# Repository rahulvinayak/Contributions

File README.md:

# Contributions

---

A collaborative repository for **Electronics-related work**, including:  
- 📐 **KiCad Schematics** – Circuit designs, PCB layouts, libraries  
- ⚡ **Embedded Code** – Firmware for microcontrollers, drivers, and RTOS examples  
- 🔧 **Hardware Notes** – Datasheets, application notes, and design references  

---

## 📂 Repository Structure  

```

  contributions/
  │
  ├── 📂 Embedded Codes/               # Firmware and embedded C/C++/Arduino/STM32/ESP32 code
  ├── 📂 kicad/                        # KiCad projects, schematics, PCB layouts
  ├── 📂 Libraries and Dependencies/     # Libraries and Dependencies used for the Codes and Projects
  ├── 📂 docs/                         # Datasheets, references, and documentation
  └── 📂 README.md                     # You are here

````

---

## 🚀 Getting Started  

1. **Clone this repo**  
```bash
   git clone https://github.com/your-username/contributions.git
   cd contributions
```

2. **Explore folders**

   * Open `.kicad_pcb` or `.sch` files with [KiCad](https://kicad.org/).
   * Build embedded code with **Arduino IDE**, **STM32CubeIDE**, **ESP IDF**, or **PlatformIO**.

---

## 🛠 Tools & Dependencies

* [KiCad](https://kicad.org/) (schematics & PCB design)
* [Arduino IDE](https://www.arduino.cc/en/software) / [PlatformIO](https://platformio.org/)
* [STM32CubeIDE](https://www.st.com/en/development-tools/stm32cubeide.html)
* [ESP-IDF](https://docs.espressif.com/projects/esp-idf/) for ESP32 projects

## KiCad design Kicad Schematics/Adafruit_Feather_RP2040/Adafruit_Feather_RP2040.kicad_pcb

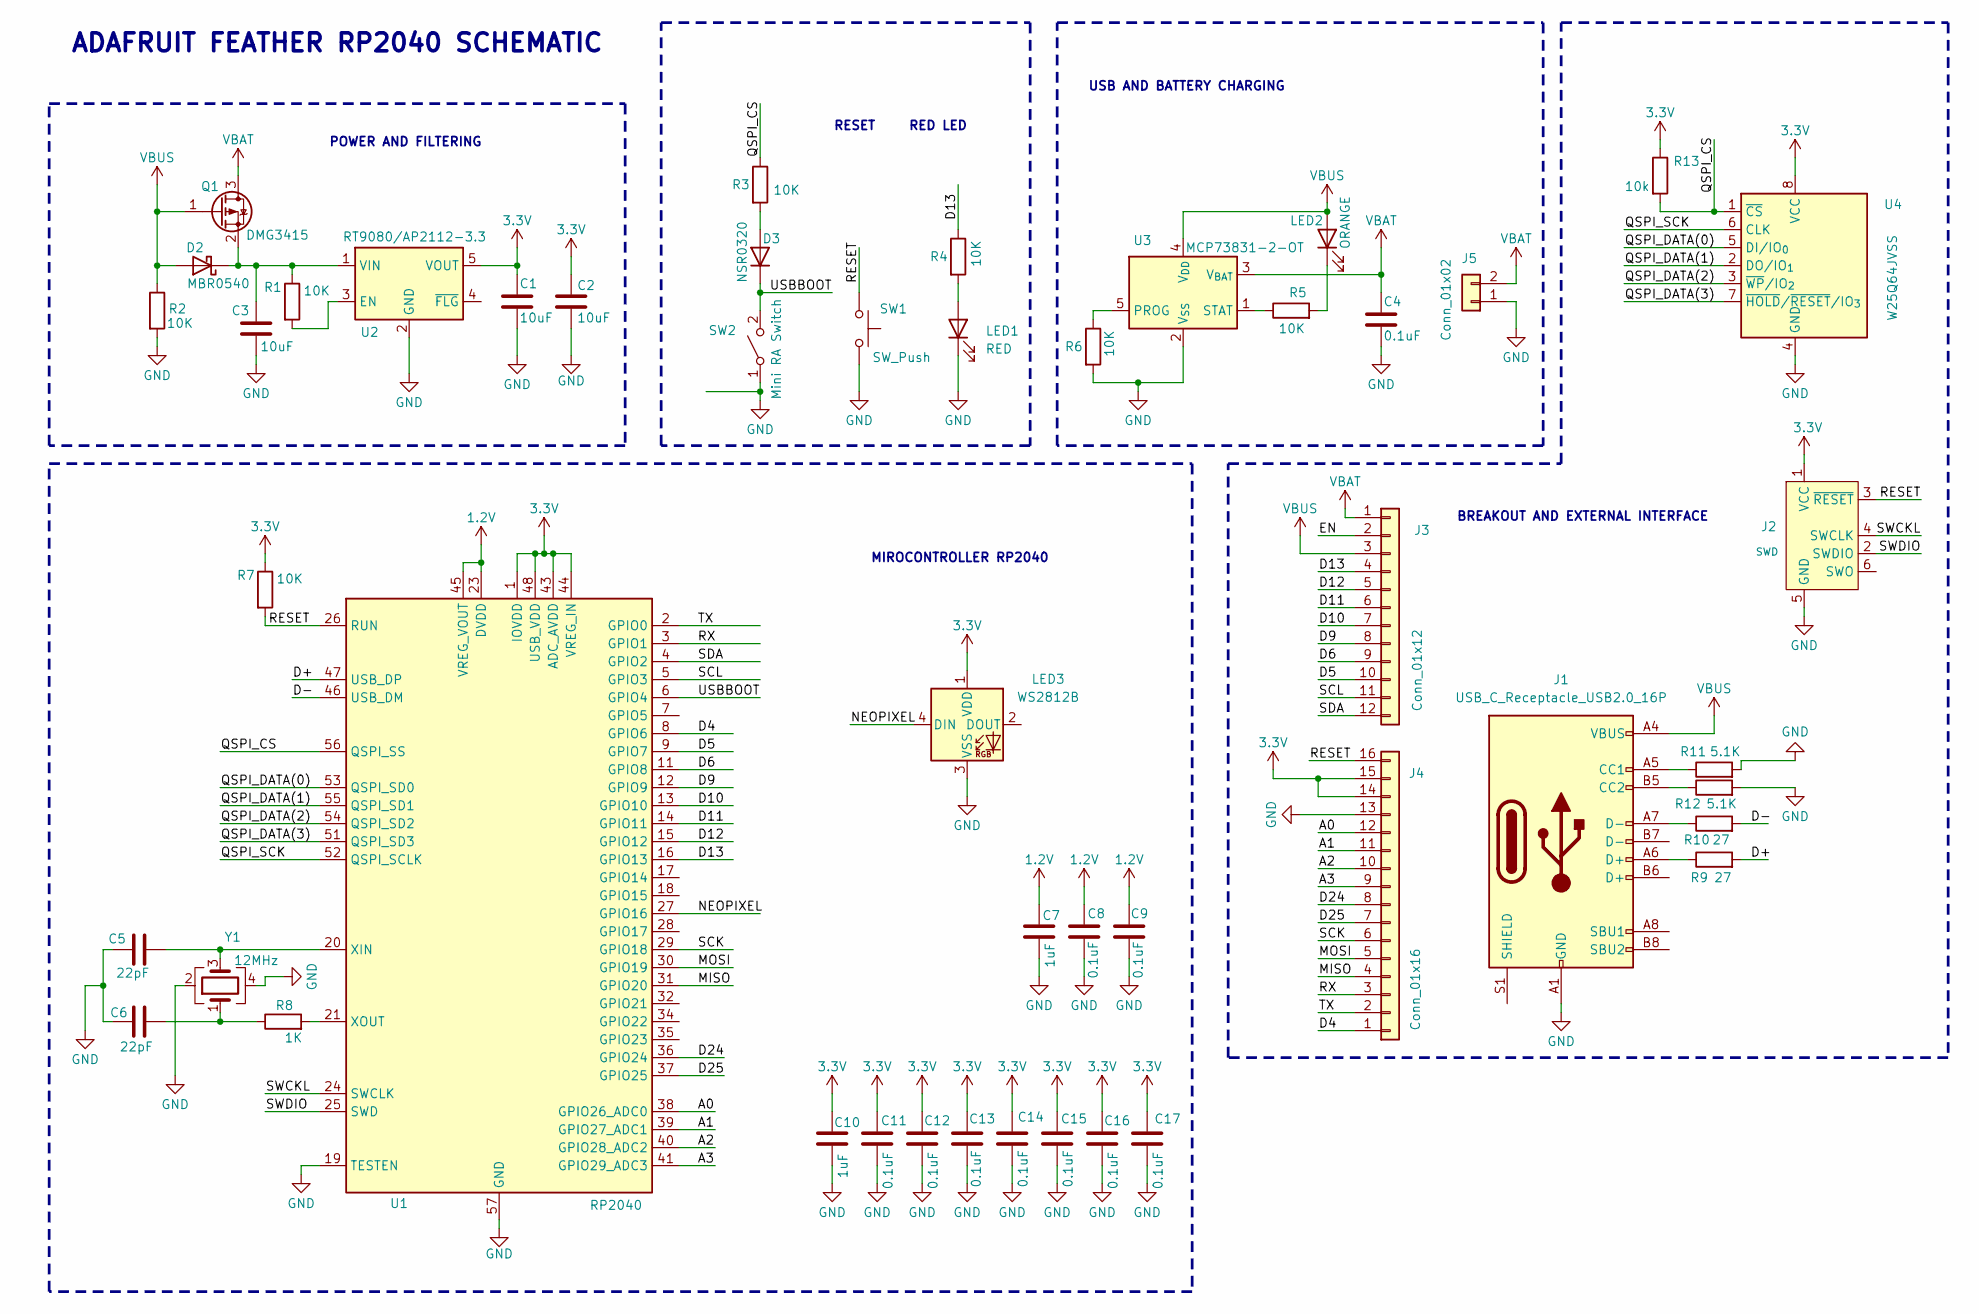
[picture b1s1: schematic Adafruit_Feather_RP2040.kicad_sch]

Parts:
C1, C2, C3: 10uF; C_0603_1608Metric
C4, C8, C9, C11, C12, C13, C14, C15, C16, C17: 0.1uF; C_0603_1608Metric
C5, C6: 22pF; C_0603_1608Metric
C7, C10: 1uF; C_0603_1608Metric
D2: MBR0540; D_SOD-123
D3: NSR0320; D_SOD-123
J1: USB_C_Receptacle_USB2.0_16P; USB_C_Receptacle_GCT_USB4105-xx-A_16P_TopMnt_Horizontal
J2: SWD; Tag-Connect_TC2030-IDC-NL_2x03_P1.27mm_Vertical
J3: Conn_01x12; PinHeader_1x12_P2.54mm_Vertical
J4: Conn_01x16; PinHeader_1x16_P2.54mm_Vertical
J5: Conn_01x02; JST_EH_S2B-EH_1x02_P2.50mm_Horizontal
LED1: RED; LED_0603_1608Metric
LED2: ORANGE; LED_0603_1608Metric
LED3: WS2812B; LED_WS2812B_PLCC4_5.0x5.0mm_P3.2mm
Q1: DMG3415; SOT-23-3
R1, R2, R3, R4, R5, R6, R7: 10K; R_0603_1608Metric
R8: 1K; R_0603_1608Metric
R9, R10: 27; R_0603_1608Metric
R11, R12: 5.1K; R_0603_1608Metric
R13: 10k; R_0603_1608Metric
SW1: SW_Push; SW_SPST_PTS810
SW2: Mini RA Switch; SW_SPST_PTS810
U1: RP2040; QFN-56-1EP_7x7mm_P0.4mm_EP3.2x3.2mm
U2: RT9080/AP2112-3.3; TSOT-23-5
U3: MCP73831-2-OT; SOT-23-5
U4: W25Q64JVSS; SOIC-8_5.3x5.3mm_P1.27mm
Y1: 12MHz; Crystal_SMD_3225-4Pin_3.2x2.5mm

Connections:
1.2V: C7.2, C8.2, C9.2, U1.23 (DVDD), U1.45 (VREG_VOUT), U1.50 (DVDD)
3.3V: C1.1, C2.1, C10.2, C11.2, C12.2, C13.2, C14.2, C15.2, C16.2, C17.2, J2.1 (VCC), J4.14, J4.15, LED3.1 (VDD), R7.1, R13.1, U1.1 (IOVDD), U1.10 (IOVDD), U1.22 (IOVDD), U1.33 (IOVDD), U1.42 (IOVDD), U1.43 (ADC_AVDD), U1.44 (VREG_IN), U1.48 (USB_VDD), U1.49 (IOVDD), U2.5 (VOUT), U4.8 (VCC)
/A0: J4.12, U1.38 (GPIO26_ADC0)
/A1: J4.11, U1.39 (GPIO27_ADC1)
/A2: J4.10, U1.40 (GPIO28_ADC2)
/A3: J4.9, U1.41 (GPIO29_ADC3)
/D4: J4.1, U1.8 (GPIO6)
/D5: J3.10, U1.9 (GPIO7)
/D6: J3.9, U1.11 (GPIO8)
/D9: J3.8, U1.12 (GPIO9)
/D10: J3.7, U1.13 (GPIO10)
/D11: J3.6, U1.14 (GPIO11)
/D12: J3.5, U1.15 (GPIO12)
/D13: J3.4, R4.1, U1.16 (GPIO13)
/D24: J4.8, U1.36 (GPIO24)
/D25: J4.7, U1.37 (GPIO25)
/D+: R9.2, U1.47 (USB_DP)
/D-: R10.2, U1.46 (USB_DM)
/EN: J3.2
/MISO: J4.4, U1.31 (GPIO20)
/MOSI: J4.5, U1.30 (GPIO19)
/NEOPIXEL: LED3.4 (DIN), U1.27 (GPIO16)
/QSPI_CS: R3.1, R13.2, U1.56 (QSPI_SS), U4.1 (~CS)
/QSPI_DATA(0): U1.53 (QSPI_SD0), U4.5 (DI/IO_{0})
/QSPI_DATA(1): U1.55 (QSPI_SD1), U4.2 (DO/IO_{1})
/QSPI_DATA(2): U1.54 (QSPI_SD2), U4.3 (~WP/IO_{2})
/QSPI_DATA(3): U1.51 (QSPI_SD3), U4.7 (~HOLD/~RESET/IO_{3})
/QSPI_SCK: U1.52 (QSPI_SCLK), U4.6 (CLK)
/RESET: J2.3 (~RESET), J4.16, R7.2, SW1.1, U1.26 (RUN)
/RX: J4.3, U1.3 (GPIO1)
/SCK: J4.6, U1.29 (GPIO18)
/SCL: J3.11, U1.5 (GPIO3)
/SDA: J3.12, U1.4 (GPIO2)
/SWCKL: J2.4 (SWCLK), U1.24 (SWCLK)
/SWDIO: J2.2 (SWDIO), U1.25 (SWD)
/TX: J4.2, U1.2 (GPIO0)
/USBBOOT: D3.1 (K), SW2.2 (B), U1.6 (GPIO4)
GND: C1.2, C2.2, C3.2, C4.2, C5.1, C6.1, C7.1, C8.1, C9.1, C10.1, C11.1, C12.1, C13.1, C14.1, C15.1, C16.1, C17.1, J1.A1 (GND), J1.A12 (GND), J1.B1 (GND), J1.B12 (GND), J2.5 (GND), J4.13, J5.1, LED1.1 (K), LED3.3 (VSS), R2.2, R6.2, R11.2, R12.2, SW1.2, SW2.1 (A), U1.19 (TESTEN), U1.57 (GND), U2.2 (GND), U3.2 (V_{SS}), U4.4 (GND), Y1.2, Y1.4
unnamed: C6.2, R8.1, Y1.1
unnamed: C3.1, D2.1 (K), Q1.2 (S), R1.1, U2.1 (VIN)
unnamed: D3.2 (A), R3.2
unnamed: J1.A5 (CC1), R11.1
unnamed: J1.B5 (CC2), R12.1
unnamed: J1.A6 (D+), R9.1
unnamed: J1.A7 (D-), R10.1
unnamed: LED1.2 (A), R4.2
unnamed: LED2.1 (K), R5.2
unnamed: C5.2, U1.20 (XIN), Y1.3
unnamed: R8.2, U1.21 (XOUT)
unnamed: R1.2, U2.3 (EN)
unnamed: R6.1, U3.5 (PROG)
unnamed: R5.1, U3.1 (STAT)
VBAT: C4.1, J3.1, J5.2, Q1.3 (D), U3.3 (V_{BAT})
VBUS: D2.2 (A), J1.A4 (VBUS), J1.A9 (VBUS), J1.B4 (VBUS), J1.B9 (VBUS), J3.3, LED2.2 (A), Q1.1 (G), R2.1, U3.4 (V_{DD})

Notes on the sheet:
USB AND BATTERY CHARGING
MIROCONTROLLER RP2040
POWER AND FILTERING
BREAKOUT AND EXTERNAL INTERFACE
RESET RED LED
ADAFRUIT FEATHER RP2040 SCHEMATIC

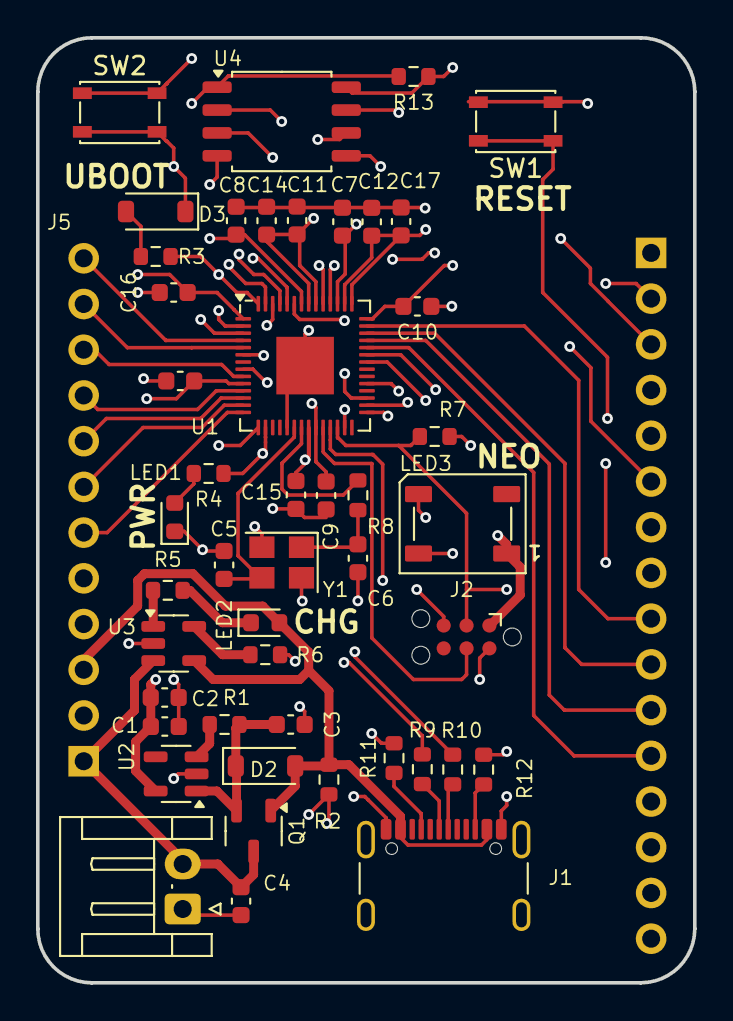
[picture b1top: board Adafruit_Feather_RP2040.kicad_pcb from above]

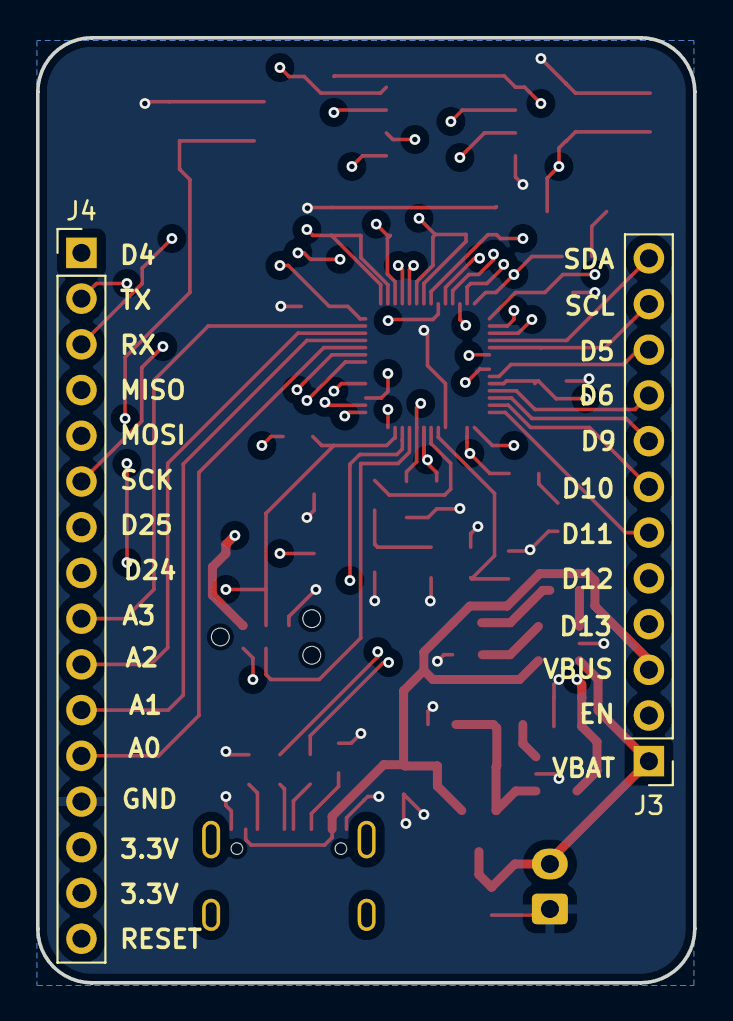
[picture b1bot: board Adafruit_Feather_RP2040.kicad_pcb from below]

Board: 4 copper layers, 36.5 x 52.5 mm, 48 parts (2 on the bottom side), 53 nets.

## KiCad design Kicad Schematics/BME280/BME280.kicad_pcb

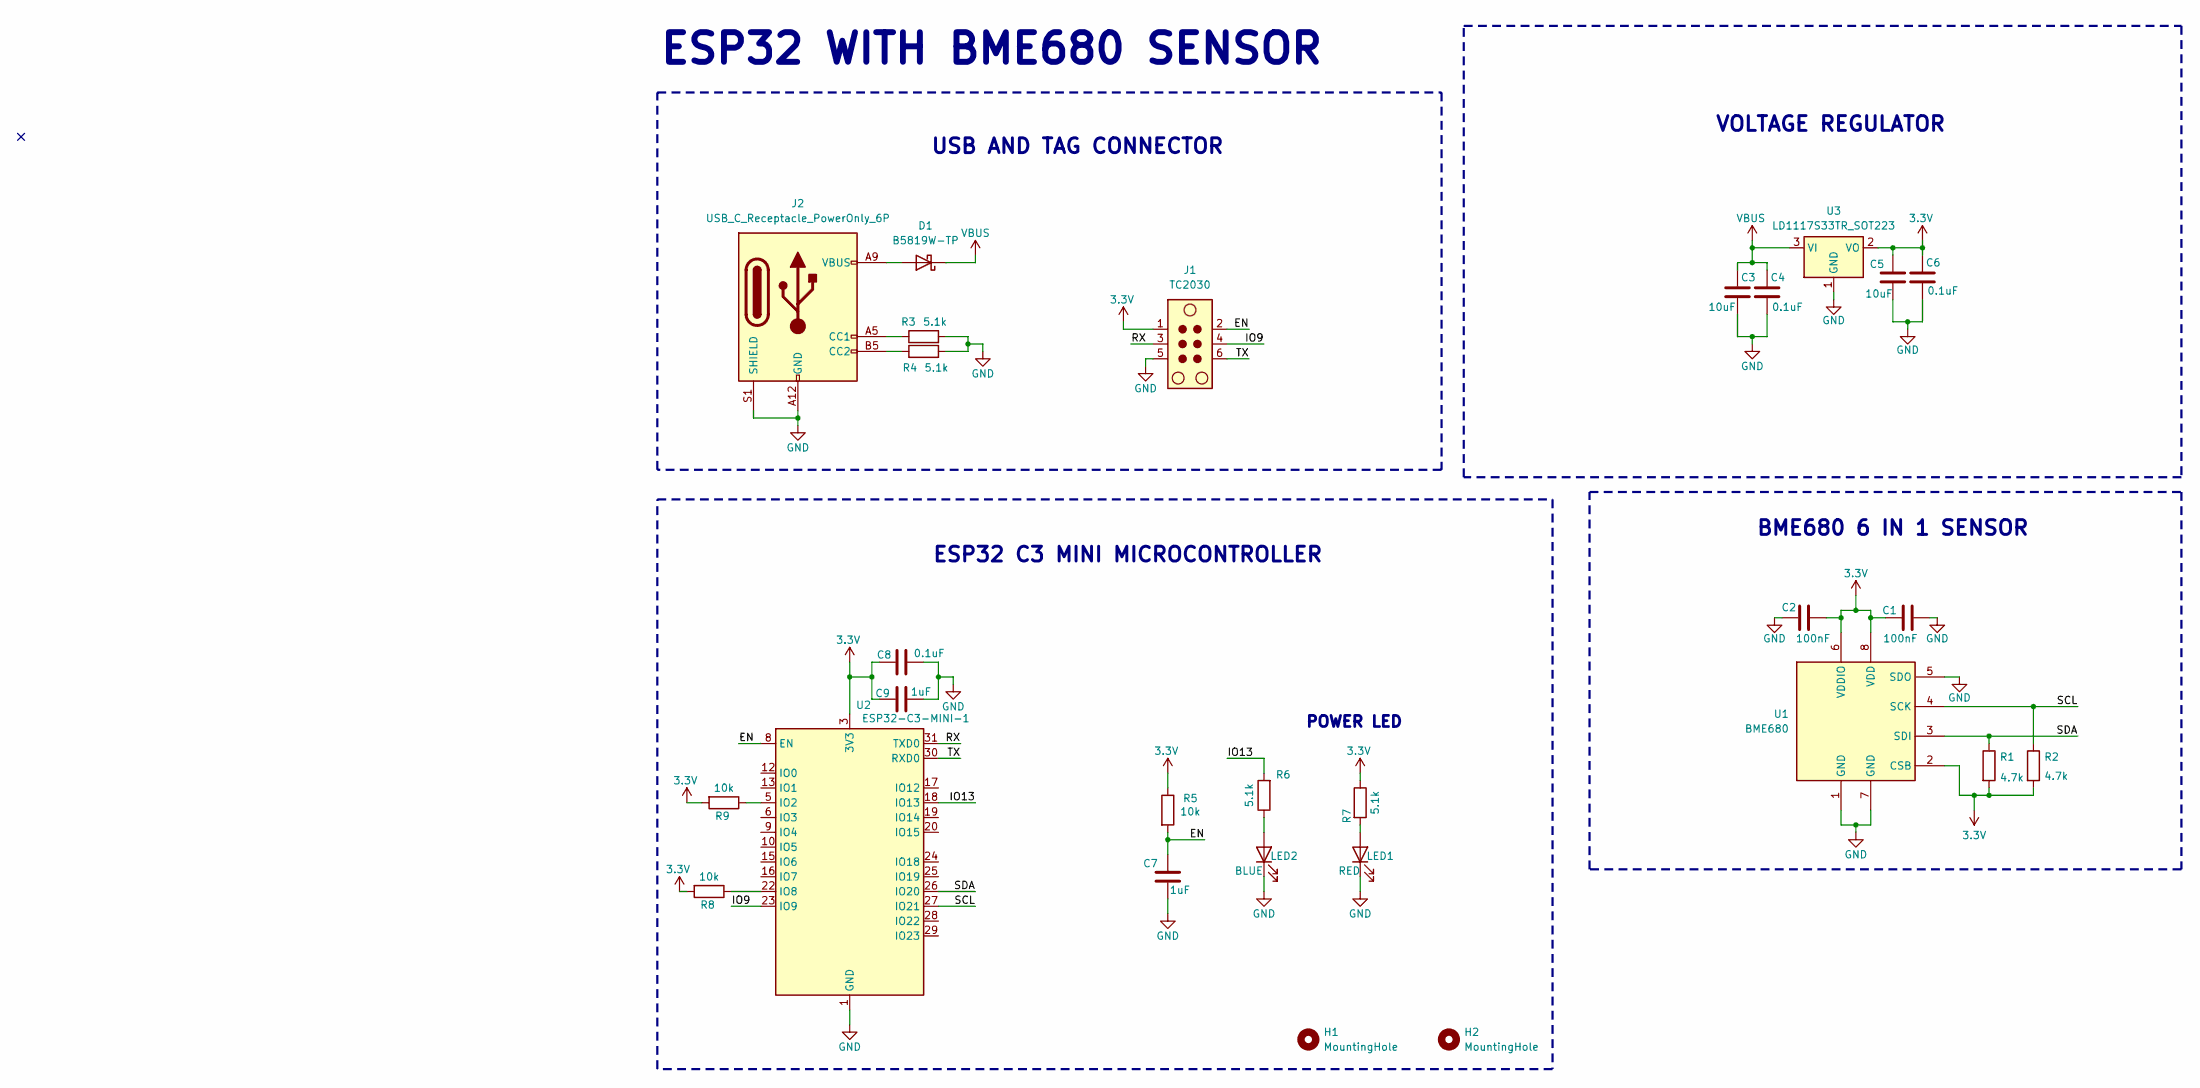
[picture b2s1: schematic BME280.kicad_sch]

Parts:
C1, C2: 100nF; C_0603_1608Metric
C3, C5: 10uF; C_0603_1608Metric
C4, C6, C8: 0.1uF; C_0603_1608Metric
C7, C9: 1uF; C_0603_1608Metric
D1: B5819W-TP; D_SOD-123
H1, H2: MountingHole; MountingHole_2.5mm
J1: TC2030; Tag-Connect_TC2030-IDC-NL_2x03_P1.27mm_Vertical
J2: USB_C_Receptacle_PowerOnly_6P; USB_C_Receptacle_GCT_USB4125-xx-x_6P_TopMnt_Horizontal
LED1: RED; LED_0603_1608Metric
LED2: BLUE; LED_0603_1608Metric
R1, R2: 4.7k; R_0603_1608Metric
R3, R4, R6, R7: 5.1k; R_0603_1608Metric
R5, R8, R9: 10k; R_0603_1608Metric
U1: BME680; Bosch_LGA-8_3x3mm_P0.8mm_ClockwisePinNumbering
U2: ESP32-C3-MINI-1; ESP32-C6-MINI-1
U3: LD1117S33TR_SOT223; SOT-223-3_TabPin2

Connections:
3.3V: C1.1, C2.2, C5.2, C6.2, C8.2, C9.2, J1.1, R1.2, R2.2, R5.1, R7.1, R8.2, R9.2, U1.2 (CSB), U1.6 (VDDIO), U1.8 (VDD), U2.3 (3V3), U3.2 (VO)
/EN: C7.1, J1.2, R5.2, U2.8 (EN)
/IO9: J1.4, U2.23 (IO9)
/IO13: R6.2, U2.18 (IO13)
/RX: J1.3, U2.31 (TXD0)
/SCL: R2.1, U1.4 (SCK), U2.27 (IO21)
/SDA: R1.1, U1.3 (SDI), U2.26 (IO20)
/TX: J1.6, U2.30 (RXD0)
GND: C1.2, C2.1, C3.1, C4.1, C5.1, C6.1, C7.2, C8.1, C9.1, J1.5, J2.A12 (GND), J2.B12 (GND), J2.S1 (SHIELD), LED1.1 (K), LED2.1 (K), R3.2, R4.2, U1.1 (GND), U1.5 (SDO), U1.7 (GND), U2.1 (GND), U2.2 (GND), U2.11 (GND), U2.14 (GND), U2.36 (GND), U2.37 (GND), U2.38 (GND), U2.39 (GND), U2.40 (GND), U2.41 (GND), U2.42 (GND), U2.43 (GND), U2.44 (GND), U2.45 (GND), U2.46 (GND), U2.47 (GND), U2.48 (GND), U2.49 (GND), U2.50 (GND), U2.51 (GND), U2.52 (GND), U2.53 (GND), U3.1 (GND)
unnamed: D1.2 (A), J2.A9 (VBUS), J2.B9 (VBUS)
unnamed: J2.A5 (CC1), R3.1
unnamed: J2.B5 (CC2), R4.1
unnamed: LED1.2 (A), R7.2
unnamed: LED2.2 (A), R6.1
unnamed: R9.1, U2.5 (IO2)
unnamed: R8.1, U2.22 (IO8)
VBUS: C3.2, C4.2, D1.1 (K), U3.3 (VI)

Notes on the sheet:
VOLTAGE REGULATOR
USB AND TAG CONNECTOR
BME680 6 IN 1 SENSOR
ESP32 C3 MINI MICROCONTROLLER
ESP32 WITH BME680 SENSOR
POWER LED

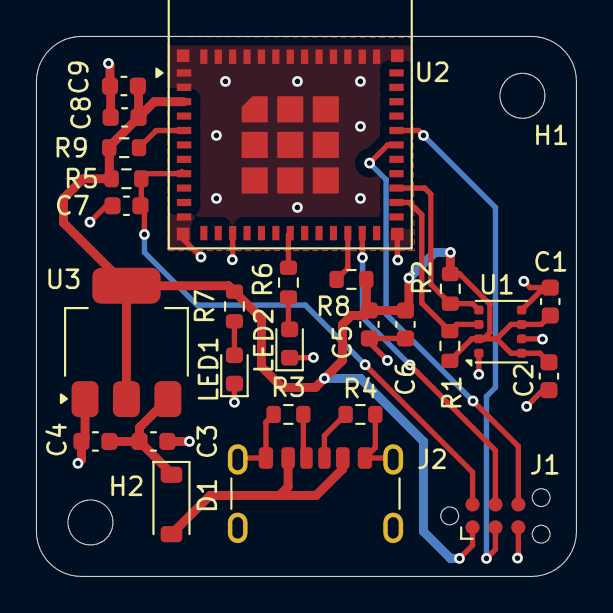
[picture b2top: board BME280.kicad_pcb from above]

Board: 2 copper layers, 30.0 x 30.0 mm, 28 parts (0 on the bottom side), 17 nets.

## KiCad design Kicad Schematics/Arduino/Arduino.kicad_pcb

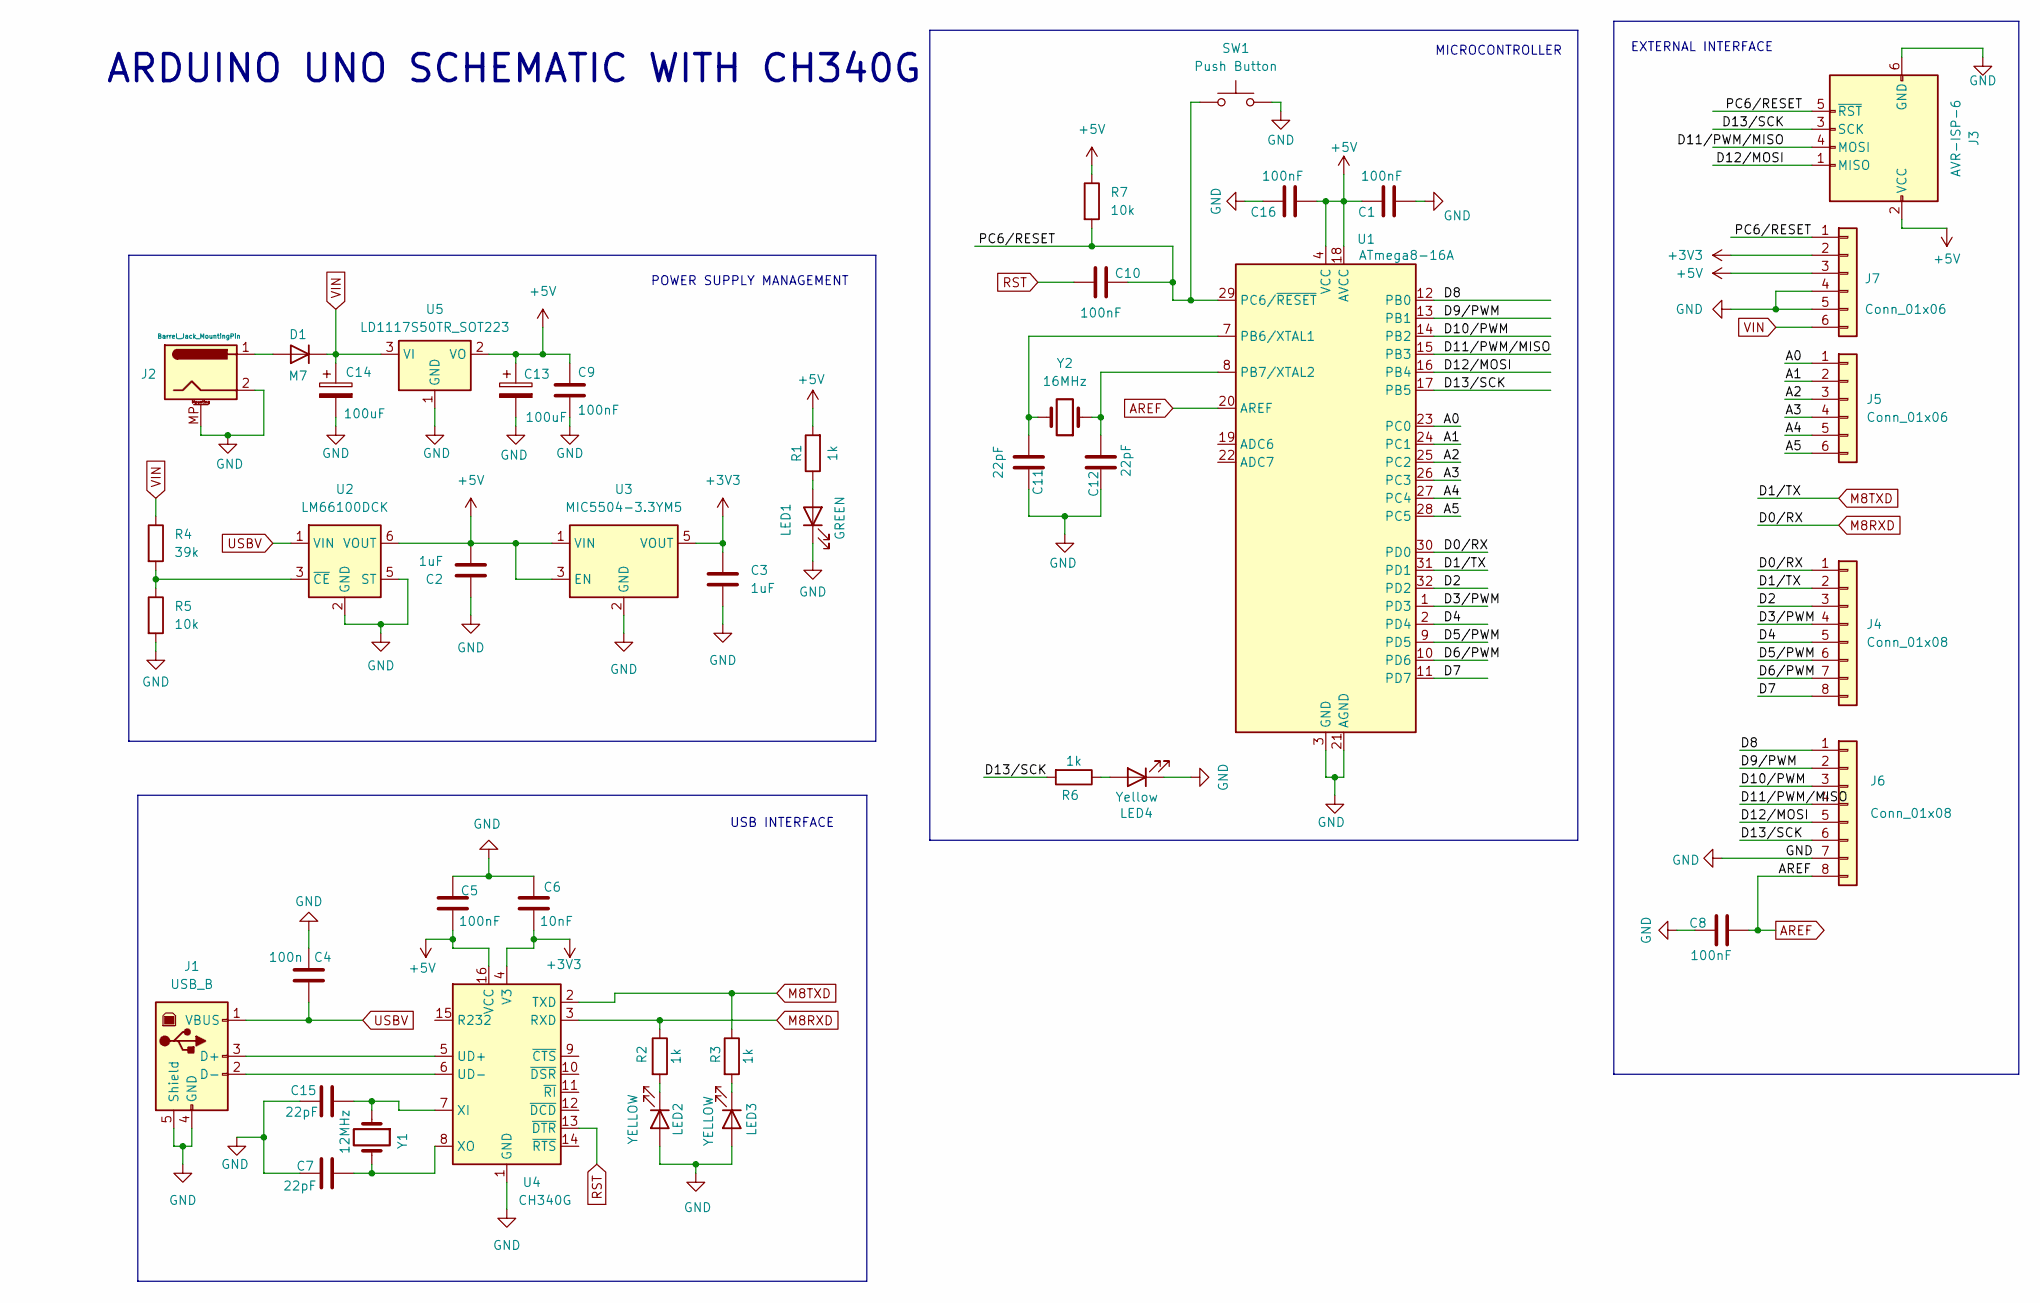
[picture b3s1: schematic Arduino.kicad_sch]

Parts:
C1, C5, C8, C9, C10, C16: 100nF; C_0603_1608Metric
C2, C3: 1uF; C_0603_1608Metric
C4: 100n; C_0603_1608Metric
C6: 10nF; C_0603_1608Metric
C7, C11, C12, C15: 22pF; C_0603_1608Metric
C13, C14: 100uF; C_Elec_6.3x5.8
D1: M7; D_SMA
J1: USB_B; USB_B_Lumberg_2411_02_Horizontal
J2: Barrel_Jack_MountingPin; BarrelJack_Horizontal
J3: AVR-ISP-6; PinHeader_2x03_P2.54mm_Vertical
J4, J6: Conn_01x08; PinSocket_1x08_P2.54mm_Vertical
J5, J7: Conn_01x06; PinSocket_1x06_P2.54mm_Vertical
LED1: GREEN; LED_0603_1608Metric
LED2, LED3: YELLOW; LED_0603_1608Metric
LED4: Yellow; LED_0603_1608Metric
R1, R2, R3, R6: 1k; R_0603_1608Metric
R4: 39k; R_0603_1608Metric
R5, R7: 10k; R_0603_1608Metric
SW1: Push Button; SW_SPST_PTS645
U1: ATmega8-16A; TQFP-32_7x7mm_P0.8mm
U2: LM66100DCK; SOT-363_SC-70-6
U3: MIC5504-3.3YM5; SOT-23-5
U4: CH340G; SO-16_5.3x10.2mm_P1.27mm
U5: LD1117S50TR_SOT223; SOT-223-3_TabPin2
Y1: 12MHz; Crystal_SMD_HC49-SD
Y2: 16MHz; Crystal_SMD_HC49-SD

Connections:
+3V3: C3.1, C6.2, J7.2, U3.5 (VOUT), U4.4 (V3)
+5V: C1.2, C2.2, C5.2, C9.1, C13.1, C16.1, J3.2 (VCC), J7.3, R1.2, R7.1, U1.4 (VCC), U1.6 (VCC), U1.18 (AVCC), U2.6 (VOUT), U3.1 (VIN), U3.3 (EN), U4.16 (VCC), U5.2 (VO)
/A0: J5.1, U1.23 (PC0)
/A1: J5.2, U1.24 (PC1)
/A2: J5.3, U1.25 (PC2)
/A3: J5.4, U1.26 (PC3)
/A4: J5.5, U1.27 (PC4)
/A5: J5.6, U1.28 (PC5)
/D2: J4.3, U1.32 (PD2)
/D3/PWM: J4.4, U1.1 (PD3)
/D4: J4.5, U1.2 (PD4)
/D5/PWM: J4.6, U1.9 (PD5)
/D6/PWM: J4.7, U1.10 (PD6)
/D7: J4.8, U1.11 (PD7)
/D8: J6.1, U1.12 (PB0)
/D9/PWM: J6.2, U1.13 (PB1)
/D10/PWM: J6.3, U1.14 (PB2)
/D11/PWM/MISO: J3.4 (MOSI), J6.4, U1.15 (PB3)
/D12/MOSI: J3.1 (MISO), J6.5, U1.16 (PB4)
/D13/SCK: J3.3 (SCK), J6.6, R6.2, U1.17 (PB5)
/PC6/RESET: C10.2, J3.5 (~RST), J7.1, R7.2, SW1.1, U1.29 (PC6/~RESET)
AREF: C8.2, J6.8, U1.20 (AREF)
GND: C1.1, C2.1, C3.2, C4.2, C5.1, C6.1, C7.2, C8.1, C9.2, C11.2, C12.2, C13.2, C14.2, C15.2, C16.2, J1.4 (GND), J1.5 (Shield), J2.2, J2.MP (MountPin), J3.6 (GND), J6.7, J7.4, J7.5, LED1.1 (K), LED2.2 (A), LED3.2 (A), LED4.1 (K), R5.2, SW1.2, U1.3 (GND), U1.5 (GND), U1.21 (AGND), U2.2 (GND), U2.5 (ST), U3.2 (GND), U4.1 (GND), U5.1 (GND)
M8RXD: J4.1, R2.1, U1.30 (PD0), U4.3 (RXD)
M8TXD: J4.2, R3.1, U1.31 (PD1), U4.2 (TXD)
unnamed: D1.2 (A), J2.1
unnamed: J1.3 (D+), U4.5 (UD+)
unnamed: J1.2 (D-), U4.6 (UD-)
unnamed: LED1.2 (A), R1.1
unnamed: LED2.1 (K), R2.2
unnamed: LED3.1 (K), R3.2
unnamed: LED4.2 (A), R6.1
unnamed: C11.1, U1.7 (PB6/XTAL1), Y2.2
unnamed: C12.1, U1.8 (PB7/XTAL2), Y2.1
unnamed: R4.2, R5.1, U2.3 (~CE)
unnamed: C15.1, U4.7 (XI), Y1.1
unnamed: C7.1, U4.8 (XO), Y1.2
RST: C10.1, U4.13 (~DTR)
USBV: C4.1, J1.1 (VBUS), U2.1 (VIN)
VIN: C14.1, D1.1 (K), J7.6, R4.1, U5.3 (VI)

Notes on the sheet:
EXTERNAL INTERFACE
ARDUINO UNO SCHEMATIC WITH CH340G
MICROCONTROLLER
POWER SUPPLY MANAGEMENT
USB INTERFACE

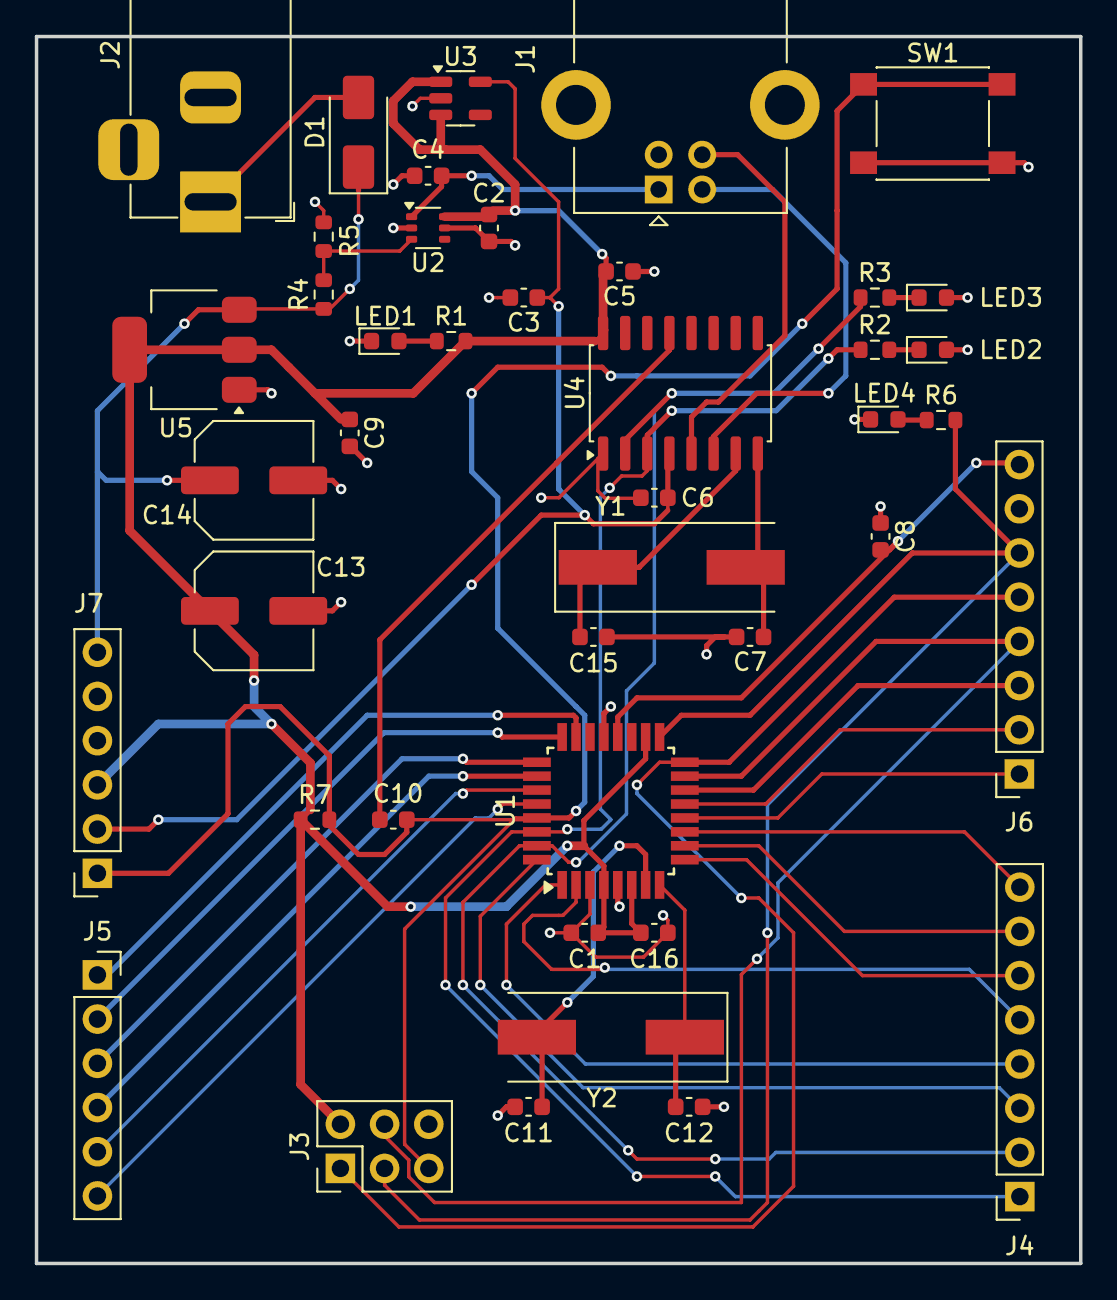
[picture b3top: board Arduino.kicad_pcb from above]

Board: 2 copper layers, 60.0 x 70.5 mm, 43 parts (0 on the bottom side), 40 nets.

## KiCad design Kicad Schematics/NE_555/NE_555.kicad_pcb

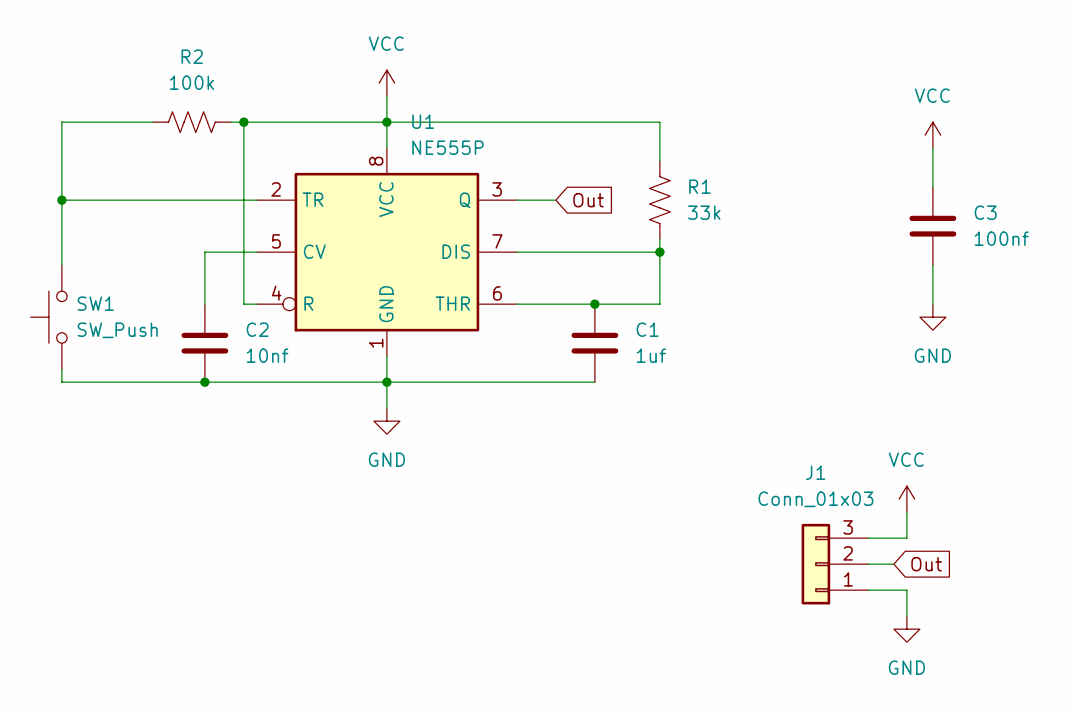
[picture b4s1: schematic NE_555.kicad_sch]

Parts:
C1: 1uf; C_0603_1608Metric
C2: 10nf; C_0603_1608Metric
C3: 100nf; C_0603_1608Metric
J1: Conn_01x03; PinHeader_1x03_P2.54mm_Vertical
R1: 33k; R_0603_1608Metric
R2: 100k; R_0603_1608Metric
SW1: SW_Push; SW_Push_1P1T_NO_Vertical_Wuerth_434133025816
U1: NE555P; SOIC-8_5.3x5.3mm_P1.27mm

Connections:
GND: C1.2, C2.2, C3.2, J1.1, SW1.1, U1.1 (GND)
unnamed: C2.1, U1.5 (CV)
unnamed: C1.1, R1.2, U1.6 (THR), U1.7 (DIS)
unnamed: R2.1, SW1.2, U1.2 (TR)
Out: J1.2, U1.3 (Q)
VCC: C3.1, J1.3, R1.1, R2.2, U1.4 (R), U1.8 (VCC)

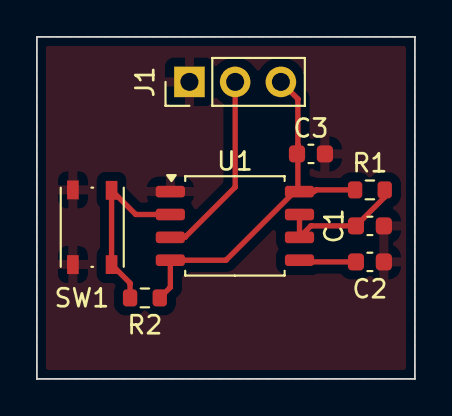
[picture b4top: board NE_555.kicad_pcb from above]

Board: 2 copper layers, 21.0 x 19.0 mm, 8 parts (0 on the bottom side), 6 nets.

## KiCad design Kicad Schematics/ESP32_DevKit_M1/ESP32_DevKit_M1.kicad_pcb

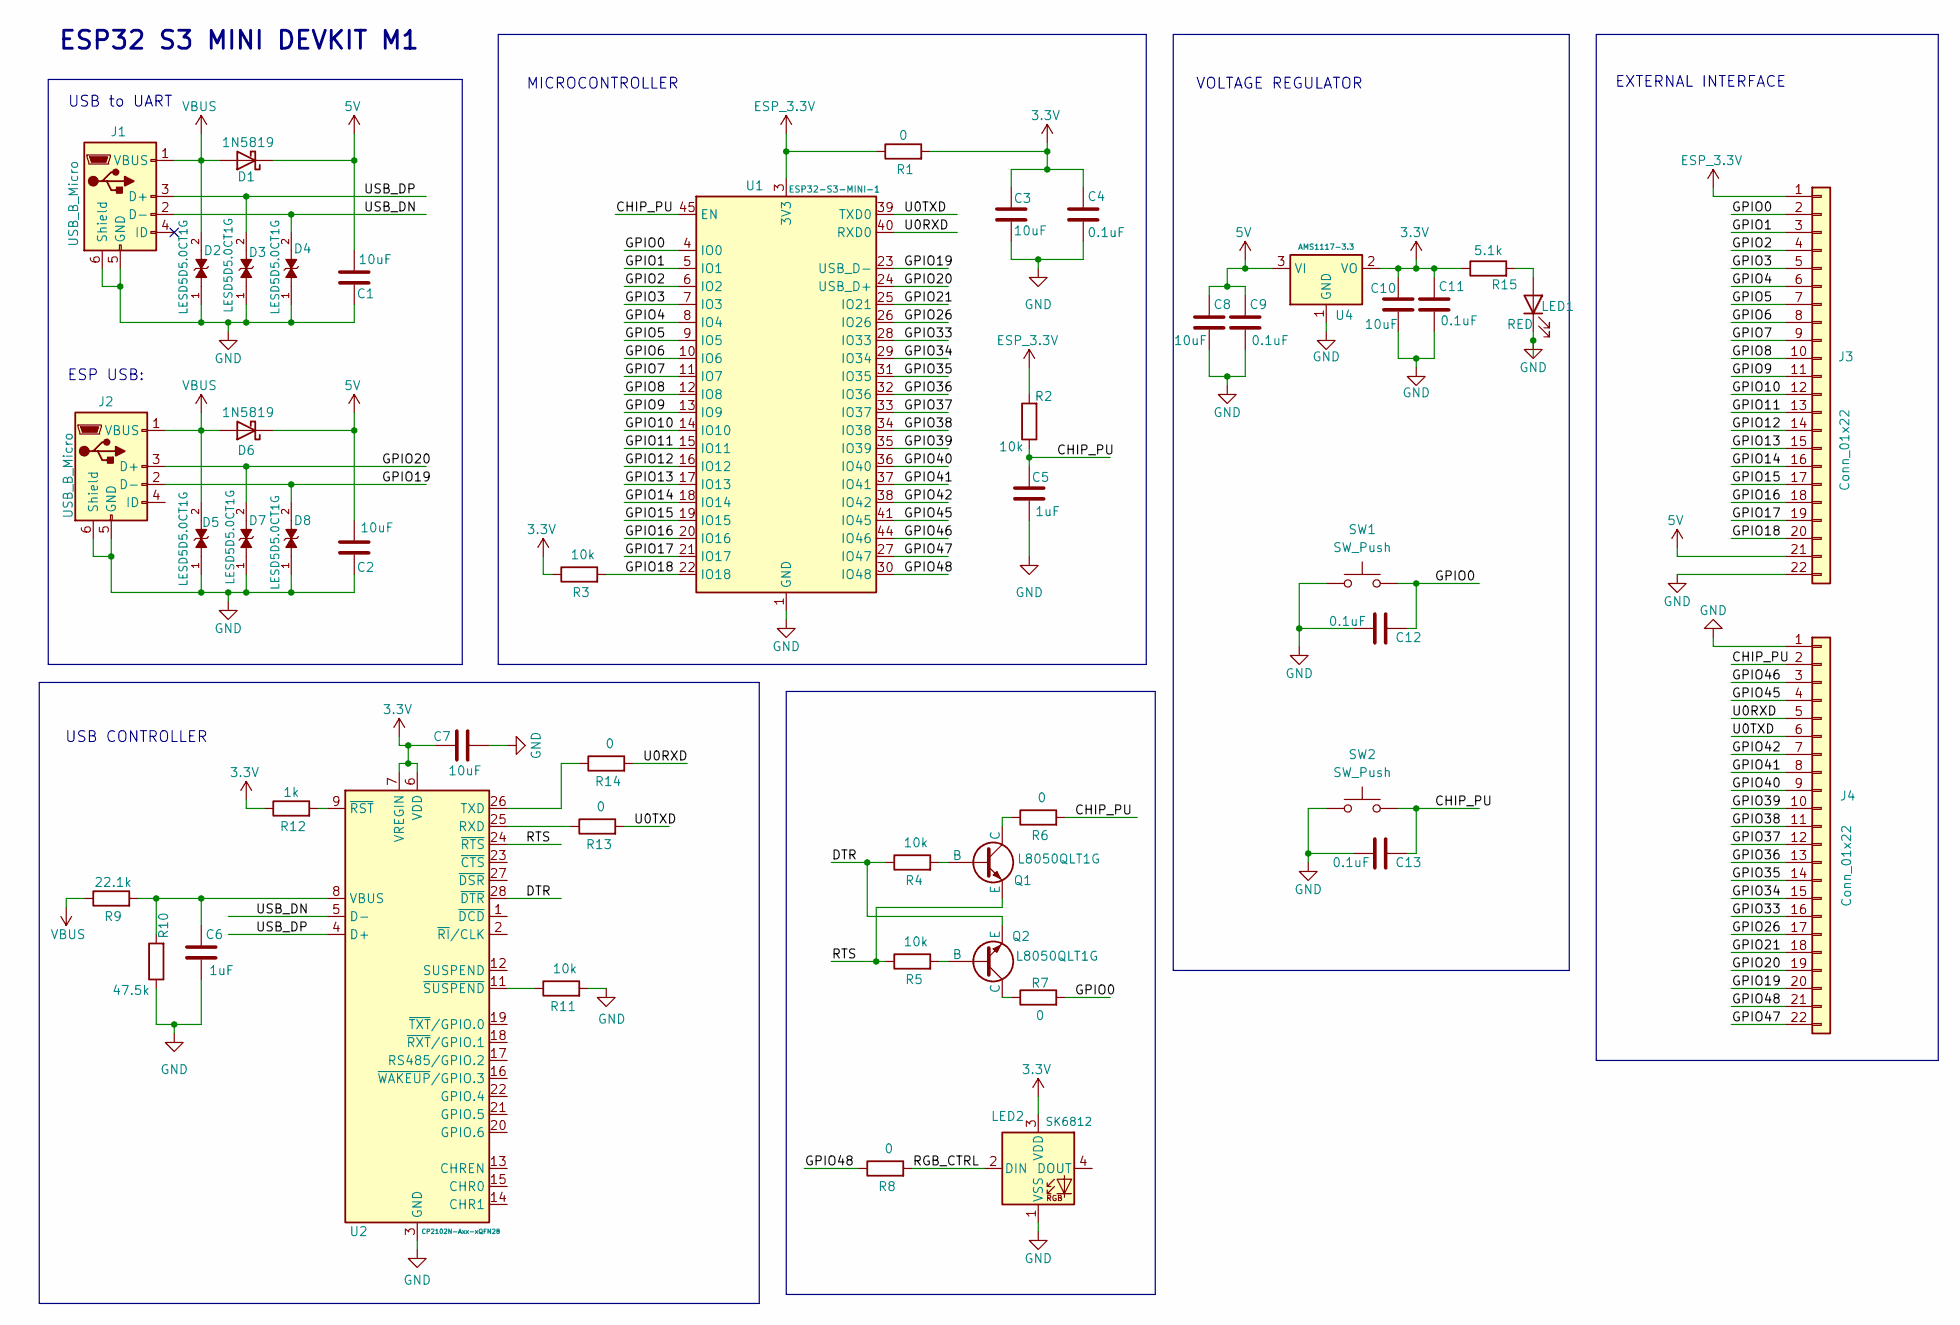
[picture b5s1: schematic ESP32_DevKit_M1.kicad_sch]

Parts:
C1, C2, C3, C7, C8, C10: 10uF; C_0603_1608Metric
C4, C9, C11, C12, C13: 0.1uF; C_0603_1608Metric
C5, C6: 1uF; C_0603_1608Metric
D1, D6: 1N5819; D_SOD-123
D2, D3, D4, D5, D7, D8: LESD5D5.0CT1G; D_SOD-523; PARTREV O
J1, J2: USB_B_Micro; USB_Micro-AB_Molex_47590-0001
J3, J4: Conn_01x22; PinHeader_1x22_P2.54mm_Vertical
LED1: RED; LED_0603_1608Metric
LED2: SK6812; LED_SK6812_PLCC4_5.0x5.0mm_P3.2mm
Q1, Q2: L8050QLT1G; SOT-23
R1, R6, R7, R8, R13, R14: 0; C_0603_1608Metric
R2, R3, R4, R5, R11: 10k; C_0603_1608Metric
R9: 22.1k; C_0603_1608Metric
R10: 47.5k; C_0603_1608Metric
R12: 1k; C_0603_1608Metric
R15: 5.1k; C_0603_1608Metric
SW1, SW2: SW_Push; SW_SPST_PTS645
U1: ESP32-S3-MINI-1; ESP32-S2-MINI-1
U2: CP2102N-Axx-xQFN28; QFN-28-1EP_5x5mm_P0.5mm_EP3.35x3.35mm
U4: AMS1117-3.3; SOT-223-3_TabPin2

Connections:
3.3V: C3.2, C4.2, C7.2, C10.2, C11.2, LED2.3 (VDD), R1.2, R3.1, R12.1, R15.1, U2.6 (VDD), U2.7 (VREGIN), U4.2 (VO)
5V: C1.1, C2.1, C8.2, C9.2, D1.1 (K), D6.1 (K), J3.21, U4.3 (VI)
/CHIP_PU: C5.2, C13.2, J4.2, R2.1, R6.2, SW2.2, U1.45 (EN)
/DTR: Q2.3 (E), R4.1, U2.28 (~DTR)
/GPIO0: C12.2, J3.2, R7.2, SW1.2, U1.4 (IO0)
/GPIO1: J3.3, U1.5 (IO1)
/GPIO2: J3.4, U1.6 (IO2)
/GPIO3: J3.5, U1.7 (IO3)
/GPIO4: J3.6, U1.8 (IO4)
/GPIO5: J3.7, U1.9 (IO5)
/GPIO6: J3.8, U1.10 (IO6)
/GPIO7: J3.9, U1.11 (IO7)
/GPIO8: J3.10, U1.12 (IO8)
/GPIO9: J3.11, U1.13 (IO9)
/GPIO10: J3.12, U1.14 (IO10)
/GPIO11: J3.13, U1.15 (IO11)
/GPIO12: J3.14, U1.16 (IO12)
/GPIO13: J3.15, U1.17 (IO13)
/GPIO14: J3.16, U1.18 (IO14)
/GPIO15: J3.17, U1.19 (IO15)
/GPIO16: J3.18, U1.20 (IO16)
/GPIO17: J3.19, U1.21 (IO17)
/GPIO18: J3.20, R3.2, U1.22 (IO18)
/GPIO19: D8.2, J2.2 (D-), J4.20, U1.23 (USB_D-)
/GPIO20: D7.2, J2.3 (D+), J4.19, U1.24 (USB_D+)
/GPIO21: J4.18, U1.25 (IO21)
/GPIO26: J4.17, U1.26 (IO26)
/GPIO33: J4.16, U1.28 (IO33)
/GPIO34: J4.15, U1.29 (IO34)
/GPIO35: J4.14, U1.31 (IO35)
/GPIO36: J4.13, U1.32 (IO36)
/GPIO37: J4.12, U1.33 (IO37)
/GPIO38: J4.11, U1.34 (IO38)
/GPIO39: J4.10, U1.35 (IO39)
/GPIO40: J4.9, U1.36 (IO40)
/GPIO41: J4.8, U1.37 (IO41)
/GPIO42: J4.7, U1.38 (IO42)
/GPIO45: J4.4, U1.41 (IO45)
/GPIO46: J4.3, U1.44 (IO46)
/GPIO47: J4.22, U1.27 (IO47)
/GPIO48: J4.21, R8.1, U1.30 (IO48)
/RGB_CTRL: LED2.2 (DIN), R8.2
/RTS: Q1.3 (E), R5.1, U2.24 (~RTS)
/U0RXD: J4.5, R14.2, U1.40 (RXD0)
/U0TXD: J4.6, R13.2, U1.39 (TXD0)
/USB_DN: D4.2, J1.2 (D-), U2.5 (D-)
/USB_DP: D3.2, J1.3 (D+), U2.4 (D+)
ESP_3.3V: J3.1, R1.1, R2.2, U1.3 (3V3)
GND: C1.2, C2.2, C3.1, C4.1, C5.1, C6.1, C7.1, C8.1, C9.1, C10.1, C11.1, C12.1, C13.1, D2.1, D3.1, D4.1, D5.1, D7.1, D8.1, J1.5 (GND), J1.6 (Shield), J2.5 (GND), J2.6 (Shield), J3.22, J4.1, LED1.1 (K), LED2.1 (VSS), R10.1, R11.2, SW1.1, SW2.1, U1.1 (GND), U1.2 (GND), U1.42 (GND), U1.43 (GND), U1.46 (GND), U1.47 (GND), U1.48 (GND), U1.49 (GND), U1.50 (GND), U1.51 (GND), U1.52 (GND), U1.53 (GND), U1.54 (GND), U1.55 (GND), U1.56 (GND), U1.57 (GND), U1.58 (GND), U1.59 (GND), U1.60 (GND), U1.61 (GND), U1.62 (GND), U1.63 (GND), U1.64 (GND), U1.65 (GND), U2.3 (GND), U2.29 (GND), U4.1 (GND)
unnamed: LED1.2 (A), R15.2
unnamed: Q1.2 (B), R4.2
unnamed: Q1.1 (C), R6.1
unnamed: Q2.2 (B), R5.2
unnamed: Q2.1 (C), R7.1
unnamed: R13.1, U2.25 (RXD)
unnamed: R14.1, U2.26 (TXD)
unnamed: C6.2, R9.2, R10.2, U2.8 (VBUS)
unnamed: R12.2, U2.9 (~RST)
unnamed: R11.1, U2.11 (~SUSPEND)
VBUS: D1.2 (A), D2.2, D5.2, D6.2 (A), J1.1 (VBUS), J2.1 (VBUS), R9.1

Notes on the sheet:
USB CONTROLLER
VOLTAGE REGULATOR
ESP32 S3 MINI DEVKIT M1
MICROCONTROLLER
ESP USB:
USB to UART
EXTERNAL INTERFACE
